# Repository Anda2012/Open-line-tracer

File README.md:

**Open source MicroPython 11-Channel PID Line Follower**

ESP32-C3 Mini-1 + Massmore JET QTR-11D

This project is a compact and accurate line follower built with an ESP32-C3 Mini-1 running MicroPython and an 11-channel Massmore JET QTR-11D reflectance sensor. It reads all sensor channels, calculates line position, and applies a tunable PID controller to drive the motors smoothly.

 Features

11-channel reflectance sensing

PID control (P, I, D adjustable in code)

Smooth PWM motor output

Simple, modular MicroPython code

Works with the DRV8833 motor driver

uses the ip5306 battery charger & boost converter

 **Project Structure**
src
 │ main.py         Main loop + motor control
 │ config.py       PID + speed settings

**Setup**

Install MicroPython on the ESP32-C3.

Upload the /src files to the board.

Adjust PID constants in config.py as needed.

Run main.py to start the line follower.

**PID Tuning Tips**

Increase P for stronger corrections.

Add I to reduce drift on long straights.

Use D to smooth out fast turns.

**License**

MIT License

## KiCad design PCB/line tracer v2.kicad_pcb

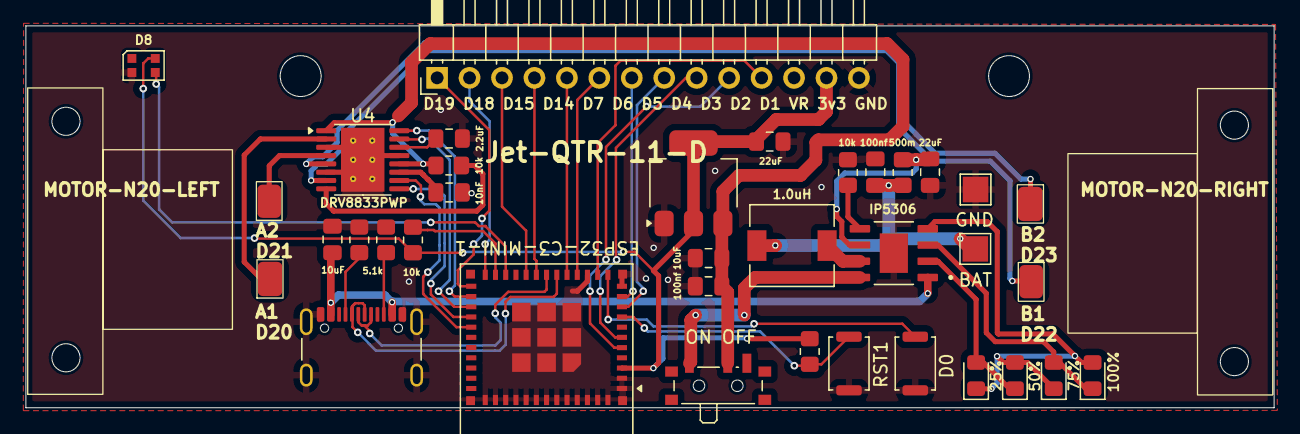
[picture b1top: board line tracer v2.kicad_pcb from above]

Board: 2 copper layers, 97.7 x 29.9 mm, 34 parts (0 on the bottom side), 42 nets.

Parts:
BAT: TestPoint; TestPoint_Pad_2.0x2.0mm
C1, C2: 22uF; C_0805_2012Metric_Pad1.18x1.45mm_HandSolder
C3: 2.2uF; C_0805_2012Metric_Pad1.18x1.45mm_HandSolder
C4, C10: 10uF; C_0805_2012Metric_Pad1.18x1.45mm_HandSolder
C5, C6: 100nf; C_0805_2012Metric_Pad1.18x1.45mm_HandSolder
C8: 10nF; C_0805_2012Metric_Pad1.18x1.45mm_HandSolder
D0: SW_Push; SW_Push_SPST_NO_Alps_SKRK
D1: 25%; LED_0805_2012Metric_Pad1.15x1.40mm_HandSolder
D2: 50%; LED_0805_2012Metric_Pad1.15x1.40mm_HandSolder
D3: 75%; LED_0805_2012Metric_Pad1.15x1.40mm_HandSolder
D4: 100%; LED_0805_2012Metric_Pad1.15x1.40mm_HandSolder
D8: WS2812B-2020; LED_WS2812B-2020_PLCC4_2.0x2.0mm
GND: TestPoint; TestPoint_Pad_2.0x2.0mm
J1: USB_C_Receptacle_USB2.0_16P; USB_C_Receptacle_GCT_USB4105-xx-A_16P_TopMnt_Horizontal
L1: 1.0uH; L_6.3x6.3_H3
MA1: Motor_DC; N20 motor
MB1: Motor_DC; N20 motor
ON OFF: SW_Push_SPDT; SW_SPDT_PCM12
R1, R3: 5.1k; R_0805_2012Metric_Pad1.20x1.40mm_HandSolder
R2: 10K; R_0805_2012Metric_Pad1.20x1.40mm_HandSolder
R4, R6, R14: 10k; R_0805_2012Metric_Pad1.20x1.40mm_HandSolder
R7: 500m; R_0805_2012Metric_Pad1.20x1.40mm_HandSolder
RST1: SW_Push; SW_Push_SPST_NO_Alps_SKRK
U1: IP5306; ip5306
U2: AMS1117-3.3; SOT-223-3_TabPin2
U3: JET-QTR-11D; PinHeader_1x14_P2.54mm_Horizontal
U4: DRV8833PWP; HTSSOP-16-1EP_4.4x5mm_P0.65mm_EP3.4x5mm_Mask2.46x2.31mm_The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
U5: ESP32-C3-MINI-1; ESP32-C6-MINI-1

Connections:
5v bat: C4.1, C6.1, ON OFF.2 (B), R6.2, U2.3 (VI), U4.1 (~SLEEP), U4.12 (VM)
5v in: ON OFF.1 (A), U1.8 (VOUT)
+3V3: C2.1, D8.4 (VDD), R2.2, R14.1, U2.2 (VO), U3.13, U5.3 (3V3)
+5V: C10.1, J1.A4 (VBUS), J1.A9 (VBUS), J1.B4 (VBUS), J1.B9 (VBUS), U1.1 (VIN)
A1: U4.16 (AIN1), U5.26 (IO20)
A2: U4.15 (AIN2), U5.27 (IO21)
B1: U4.9 (BIN1), U5.28 (IO22)
B2: U4.10 (BIN2), U5.29 (IO23)
BAT: BAT.1, C5.1, L1.2, R7.1
D1: U3.11, U5.13 (IO1)
D2: U3.10, U5.5 (IO2)
D3: U3.9, U5.6 (IO3)
D4: U3.8, U5.9 (IO4)
D5: U3.7, U5.10 (IO5)
D6: U3.6, U5.15 (IO6)
D7: U3.5, U5.16 (IO7)
D14: U3.4, U5.19 (IO14)
D15: U3.3, U5.20 (IO15)
D18: U3.2, U5.24 (IO18)
D19: U3.1, U5.25 (IO19)
D+: J1.A6 (D+), J1.B6 (D+), U5.18 (IO13)
D-: J1.A7 (D-), J1.B7 (D-), U5.17 (IO12)
EN: R2.1, RST1.1, U5.8 (EN)
GND: C1.2, C2.2, C3.2, C4.2, C5.2, C6.2, C8.1, C10.2, D0.2, D8.2 (VSS), GND.1, J1.A1 (GND), J1.A12 (GND), J1.B1 (GND), J1.B12 (GND), J1.S1 (SHIELD), R1.2, R3.2, R4.1, RST1.2, U1.9 (POWERPAD), U2.1 (GND), U3.14, U4.3 (AISEN), U4.6 (BISEN), U4.13 (GND), U4.17 (GND), U5.1 (GND), U5.2 (GND), U5.11 (GND), U5.14 (GND), U5.36 (GND), U5.37 (GND), U5.38 (GND), U5.39 (GND), U5.40 (GND), U5.41 (GND), U5.42 (GND), U5.43 (GND), U5.44 (GND), U5.45 (GND), U5.46 (GND), U5.47 (GND), U5.48 (GND), U5.49 (GND), U5.50 (GND), U5.51 (GND), U5.52 (GND), U5.53 (GND)
IO0: D0.1, U5.12 (IO0)
N1A: MA1.1 (+), U4.2 (AOUT1)
N1B: MA1.2 (-), U4.4 (AOUT2)
N2A: MB1.2 (-), U4.7 (BOUT1)
N2B: MB1.1 (+), U4.5 (BOUT2)
unnamed: D1.2 (A), D2.1 (K), U1.2 (LED1)
unnamed: D1.1 (K), D2.2 (A), D3.1 (K), D4.2 (A), U1.4 (LED3)
unnamed: D3.2 (A), D4.1 (K), U1.3 (LED2)
unnamed: D8.3 (DIN), U5.22 (IO8)
unnamed: J1.A5 (CC1), R1.1
unnamed: J1.B5 (CC2), R3.1
unnamed: C1.1, R7.2, U1.6 (BAT)
unnamed: R4.2, U1.5 (KEY)
unnamed: L1.1, U1.7 (SW)
unnamed: C8.2, U4.11 (VCP)
unnamed: C3.1, U4.14 (VINT)
unnamed: R6.1, U4.8 (~FAULT)
unnamed: R14.2, U5.23 (IO9)

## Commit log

2025-11-24 Create placeholder
